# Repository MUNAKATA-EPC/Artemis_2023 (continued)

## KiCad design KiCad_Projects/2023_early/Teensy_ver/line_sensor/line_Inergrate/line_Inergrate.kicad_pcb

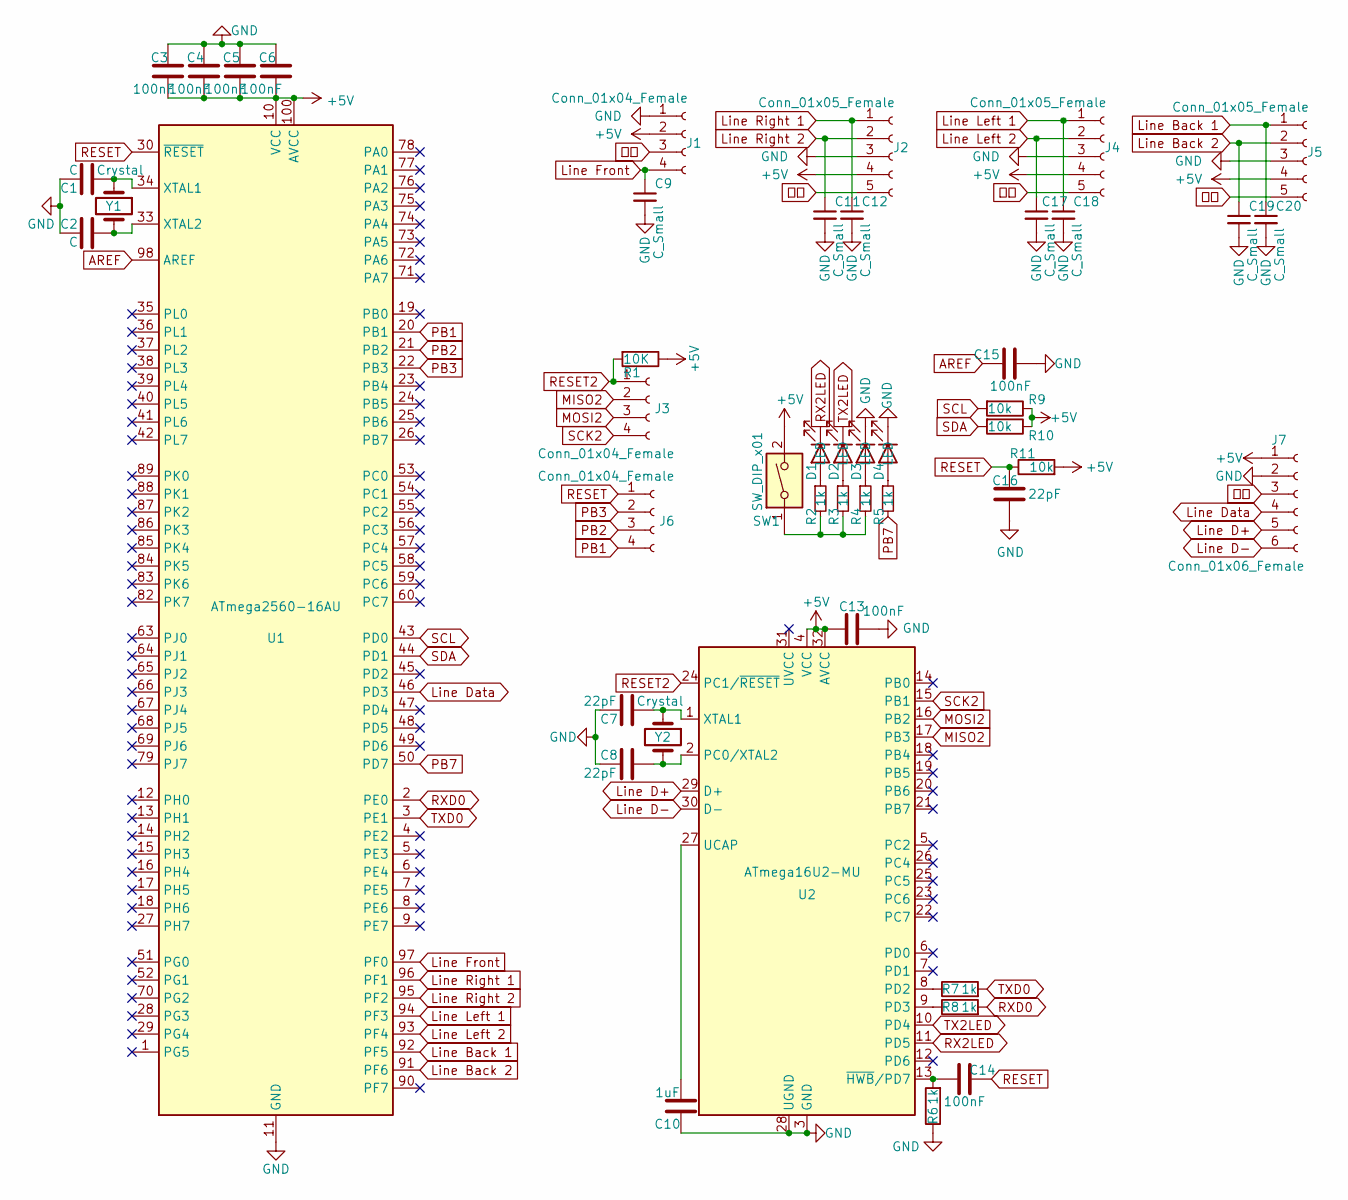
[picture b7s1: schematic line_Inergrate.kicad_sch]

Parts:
C1, C2: C; C_0402_1005Metric; LCSC C1555
C3, C4, C5, C6, C13, C14, C15: 100nF; C_0402_1005Metric; LCSC C41851
C7, C8, C16: 22pF; C_0402_1005Metric; LCSC C1555
C9, C11, C12, C17, C18, C19, C20: C_Small; C_Disc_D3.0mm_W1.6mm_P2.50mm
C10: 1uF; C_0402_1005Metric; LCSC C167339
D1, D2, D3, D4: LED; LED_0402_1005Metric; LCSC C130725
J1: Conn_01x04_Female; PinSocket_1x04_P2.54mm_Horizontal
J2, J4, J5: Conn_01x05_Female; PinSocket_1x05_P2.54mm_Horizontal
J3, J6: Conn_01x04_Female; PinSocket_1x04_P2.54mm_Vertical
J7: Conn_01x06_Female; JST_XH_B6B-XH-A_1x06_P2.50mm_Vertical
R1: 10K; R_0402_1005Metric; LCSC C25744
R2, R3, R4, R5: 1k; R_0402_1005Metric; LCSC C11702
R6, R7, R8: 1k; R_0402_1005Metric; LCSC C105637
R9, R10, R11: 10k; R_0402_1005Metric; LCSC C25744
SW1: SW_DIP_x01; 2MS1T2B4M2QES
U1: ATmega2560-16AU; TQFP-100_14x14mm_P0.5mm
U2: ATmega16U2-MU; QFN-32-1EP_5x5mm_P0.5mm_EP3.1x3.1mm
Y1, Y2: Crystal; Crystal_SMD_3225-4Pin_3.2x2.5mm; LCSC C164049

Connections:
Line Left 1: C18.1, J4.1, U1.94 (PF3)
+5V: C3.2, C4.2, C5.2, C6.2, C13.2, J1.2, J2.4, J4.4, J5.4, J7.1, R1.1, R9.1, R10.1, R11.2, SW1.2, U1.10 (VCC), U1.31 (VCC), U1.61 (VCC), U1.80 (VCC), U1.100 (AVCC), U2.4 (VCC), U2.32 (AVCC)
AREF: C15.1, U1.98 (AREF)
GND: C1.2, C2.2, C3.1, C4.1, C5.1, C6.1, C7.2, C8.2, C9.2, C10.2, C11.2, C12.2, C13.1, C15.2, C16.2, C17.2, C18.2, C19.2, C20.2, D3.1 (K), D4.1 (K), J1.1, J2.3, J4.3, J5.3, J7.2, R6.1, U1.11 (GND), U1.32 (GND), U1.62 (GND), U1.81 (GND), U1.99 (GND), U2.3 (GND), U2.28 (UGND), U2.33 (GND)
Line Back 1: C20.1, J5.1, U1.92 (PF5)
Line Back 2: C19.1, J5.2, U1.91 (PF6)
Line D+: J7.5, U2.29 (D+)
Line D-: J7.6, U2.30 (D-)
Line Data: J7.4, U1.46 (PD3)
Line Front: C9.1, J1.4, U1.97 (PF0)
Line Left 2: C17.1, J4.2, U1.93 (PF4)
Line Right 1: C12.1, J2.1, U1.96 (PF1)
Line Right 2: C11.1, J2.2, U1.95 (PF2)
MISO2: J3.2, U2.17 (PB3)
MOSI2: J3.3, U2.16 (PB2)
unnamed: C1.1, U1.34 (XTAL1), Y1.1
unnamed: C2.1, U1.33 (XTAL2), Y1.2
unnamed: C7.1, U2.1 (XTAL1), Y2.1
unnamed: C8.1, U2.2 (PC0/XTAL2), Y2.2
unnamed: C10.1, U2.27 (UCAP)
unnamed: C14.1, R6.2, U2.13 (~HWB/PD7)
unnamed: D1.2 (A), R2.1
unnamed: D2.2 (A), R3.1
unnamed: D3.2 (A), R4.1
unnamed: D4.2 (A), R5.1
unnamed: R2.2, R3.2, R4.2, SW1.1
unnamed: R7.1, U2.8 (PD2)
unnamed: R8.1, U2.9 (PD3)
PB1: J6.4, U1.20 (PB1)
PB2: J6.3, U1.21 (PB2)
PB3: J6.2, U1.22 (PB3)
PB7: R5.2, U1.50 (PD7)
RESET: C14.2, C16.1, J6.1, R11.1, U1.30 (~RESET)
RESET2: J3.1, R1.2, U2.24 (PC1/~RESET)
RX2LED: D1.1 (K), U2.11 (PD5)
RXD0: R8.2, U1.2 (PE0)
SCK2: J3.4, U2.15 (PB1)
SCL: R9.2, U1.43 (PD0)
SDA: R10.2, U1.44 (PD1)
TX2LED: D2.1 (K), U2.10 (PD4)
TXD0: R7.2, U1.3 (PE1)
可変: J1.3, J2.5, J4.5, J5.5, J7.3

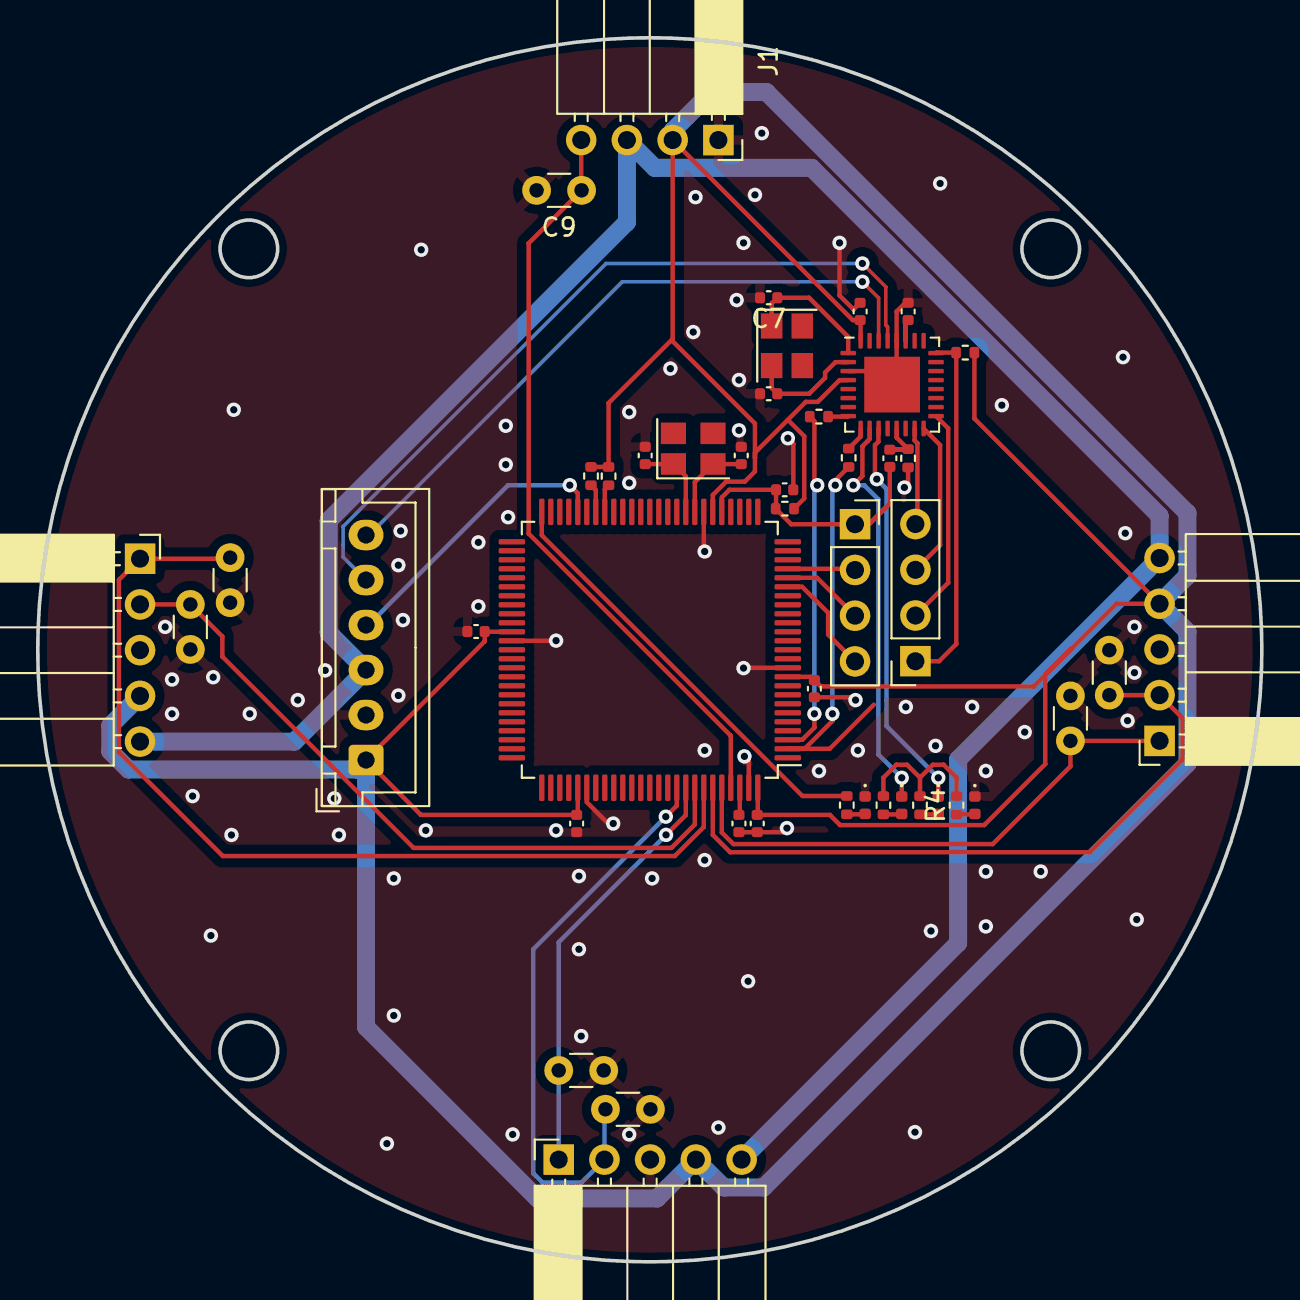
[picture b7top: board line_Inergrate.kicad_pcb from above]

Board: 2 copper layers, 68.0 x 68.0 mm, 46 parts (0 on the bottom side), 42 nets.

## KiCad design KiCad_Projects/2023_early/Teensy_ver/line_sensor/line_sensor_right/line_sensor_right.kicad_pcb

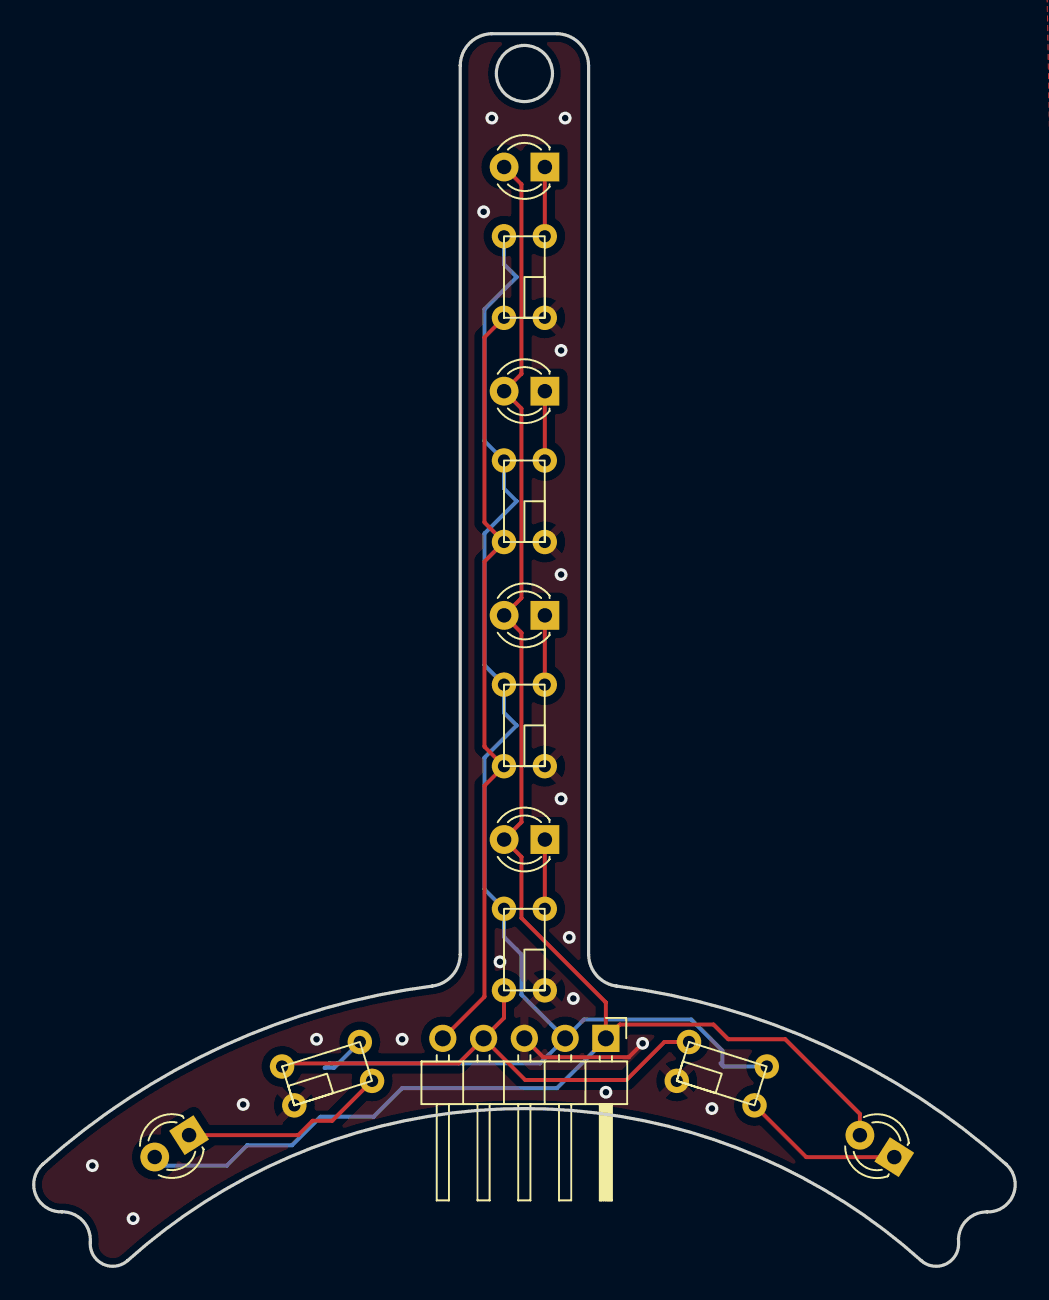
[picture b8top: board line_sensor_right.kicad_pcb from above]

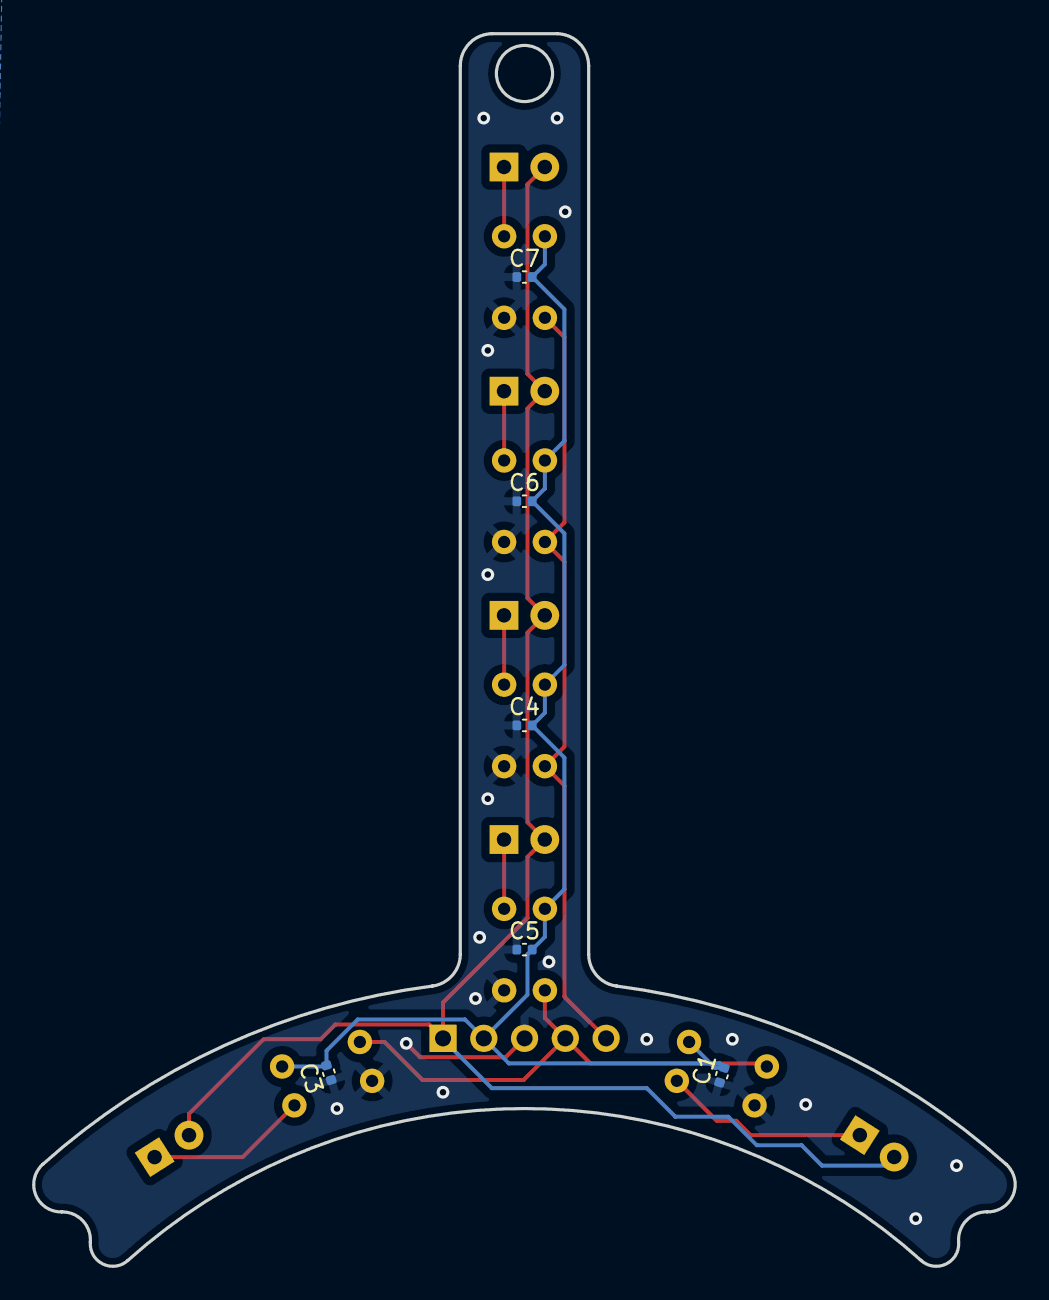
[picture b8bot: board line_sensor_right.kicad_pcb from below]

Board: 2 copper layers, 61.2 x 76.8 mm, 19 parts (6 on the bottom side), 11 nets.

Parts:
C1, C3, C4, C5, C6, C7: C_Small; C_0402_1005Metric
D1, D3, D4, D5, D6, D7: LED; LED_D3.0mm_Clear
J1: Conn_01x05_Female; PinHeader_1x05_P2.54mm_Horizontal
U1, U3, U4, U5, U6, U7: Line_sennsor

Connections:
+5V: C1.2, C3.2, C4.2, C5.2, C6.2, C7.2, J1.2, U1.2 (VCC), U3.2 (VCC), U4.2 (VCC), U5.2 (VCC), U6.2 (VCC), U7.2 (VCC)
GND: C1.1, C3.1, C4.1, C5.1, C6.1, C7.1, J1.3, U1.4 (GND), U3.4 (GND), U4.4 (GND), U5.4 (GND), U6.4 (GND), U7.4 (GND)
Line Data 1: J1.4, U1.3 (VOUT), U3.3 (VOUT), U5.3 (VOUT)
Line Data 2: J1.5, U4.3 (VOUT), U6.3 (VOUT), U7.3 (VOUT)
unnamed: D1.1 (K), U1.1 (K(-))
unnamed: D3.1 (K), U3.1 (K(-))
unnamed: D4.1 (K), U4.1 (K(-))
unnamed: D5.1 (K), U5.1 (K(-))
unnamed: D6.1 (K), U6.1 (K(-))
unnamed: D7.1 (K), U7.1 (K(-))
R Trim: D1.2 (A), D3.2 (A), D4.2 (A), D5.2 (A), D6.2 (A), D7.2 (A), J1.1

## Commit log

2022-04-20 Initial Commit
    最初のコミットです。
    各ファイルを追加。
2022-04-20 進捗追加
    githubリポジトリを作成
2022-04-21 Revert "Update New-Robo-DesignMemo.txt"
    This reverts commit f9405847499580822d066fcdcb91f958b3cb44ed.
2022-04-21 ジャイロセンサ用ファイルの生成
    VSCode(PlatformIO)の自動生成ファイル
2022-04-21 CADデータ用ファイル追加
2022-04-21 .gitkeepファイルの追加
    このファイルは空フォルダがコミット内容として反映されるために追加する空ファイルです。
    ディレクトリを作成した際に中身が空だった場合は.gitkeepファイルを生成してコミット内容に反映してください。
2022-04-21 空フォルダの反映
    .gitkeepファイルの追加
2022-04-21 README.MD の追加によるファイル削除
    ロボットの情報をREADME.MDに追加したことによるファイルの削除。
    要望があったらまた追加します。
2022-04-21 Revert "フレーム 現状 Artemis機"
    This reverts commit 175b8af8b3617812aba4bc7054874700fb0bbe0f.
2022-04-27 DSR1202用のライブラリ追加
    https://github.com/anbara/DSR-1202 より引用
2022-04-29 過去ファイル追加&ジャイロプロジェクト名変更
    福岡ノード2021用のフォルダ作成。
    過去のプログラム置き場作成。
    ジャイロをMPU6050からL3GD20に変更。
2022-05-03 MPU6050用のジャイロファイルをリターン・ファイル整理
    MPU6050用のプログラムを保存しておきます
    あとファイルをまとめておきました。
2022-05-03 セカンドロボットの文化祭用プログラム追加
    ジャイロと電源の部分一緒に作ってるから
    pid動かないと思うの！！！！(正解)
2022-05-03 readme.mdにライセンス追加
2022-06-01 KiCadプロジェクト保存用フォルダの作成
    バックアップはちゃんと取りましょう。
2022-06-01 部品ごとのデータファイルの追加
    マイコンのシンボル、基板のデータ保存用のファイル等の追加
2022-06-01 omuniのCADデータの追加
    各部品のデータの追加
    ３Dプリンター用のデータにも変換済み
2022-06-07 KiCadの各プロジェクトの追加
    各シンボルのライブラリ・プロジェクトの追加
2022-06-07 シンボルライブラリのパス指定を絶対パスから相対パスへ変更。
    環境によってプロジェクトの配置階層が変わるのでプロジェクトから見た相対パスへ変更。
    ${KIPRJMOD}/../Lib/(project_name)
    で指定可能なのでこれからはそうすること。
2022-06-07 メイン基板の更新
    IRセンサー等のセンサー追加、配線追加。
2022-06-08 メイン基板の更新
    IRセンサの配線変更等
2022-06-09 メイン基板の更新
    内容は知らないです
2022-06-09 基板の更新
    メイン基板の更新、ライブラリの追加
    ※電源基盤はいまだ理解できずに手が付けられてない。
2022-06-12 基板データの更新
    メイン基板、電源基盤のデータ更新
    回路が正しいか答え合わせするもんなくで困ってる。ダレカタスケテ
2022-06-13 基板データの更新
    電源回路の更新、ライブラリの追加
    やっと回路理解してきた！
2022-06-14 基板データの更新
    電源基盤の更新、フットプリントの割り当て中
2022-06-17 基盤データの更新
    電源基盤のフットプリントの割り当て完了
    配線開始。
2022-06-20 基盤データの更新
    フットプリントの更新、電源基盤の部品の配置
2022-06-22 電源基盤の更新
    基盤の外形のインポート、部品の配置。
2022-06-24 基盤データの更新
    電源基盤、IOボードの配線更新。
2022-06-24 基盤データの更新
    メイン基板の回路図の更新
2022-06-29 基盤データのアップデート
    ローカルコミットはちゃんと作ってください
2022-06-29 基板データの更新
    ラインセンサーの完成
    Arduino メイン基板の作成、製作開始。
2022-06-30 基板データの更新
    IO基板、ライン基板、電源基盤のコネクタ変更、最終確認
    メイン基板制作中。
2022-07-01 基板データの更新
    メイン基板の製作
2022-07-02 基板データの更新
    メイン基板の部品配置まででけた
2022-07-03 AE-BNO055-BO専用のプロジェクト追加
2022-07-10 基板データの更新
    最後に更新してからのデータ全てです。
2022-07-10 基板データの更新
    今日変更した分
    メイン基板
2022-07-11 基板データの更新
    最新バージョンの発注データの作成
    最新バージョンの発注。
2022-07-13 基板データの更新
    メイン基板データの更新
2022-07-18 基板データの更新
    IO基板のCNCバージョン作成
2022-07-18 基板データの更新
    IO基板
2022-07-18 部内大会用のプログラムファイル追加
    タイトル通り。
    松田の前代ロボに関してはプログラムはほぼ完ぺき。
2022-07-18 基板データの更新
    新メイン基板の回路図の作成。
2022-07-18 Revert "Merge branch 'main' of https://github.com/MUNAKATA-EPC/Munachu_Artemis"
    This reverts commit 2d62b7fa3f437b1c22d560bdfdc29bbce9a662c6, reversing
    changes made to e44e47092be221c5dedf368005a17df58de841e6.
2022-07-24 基板データの更新
2022-07-24 Dual core TJ3B ファイルの作成
    ただいまスレーブを用いた20ポートTJ3Bの製作中です。
    今、回路設計中。
2022-07-27 基板データの更新
    新メイン基板あたりをいじった
2022-07-28 部内大会用プログラムの作成
    部内大会というか、北九州オープンくらいまでのプログラムが入ってます。
    カメラ・IR_ring・Line_ringの制御。
2022-07-28 基板データの更新
    いろいろいじったものの更新です。
    MD用のファイルの追加もしました。
2022-07-31 Gitの変更多すぎだろ！
    ここに覚えてる限りの変更点をまとめます
    ・カメラのプログラム
    ・IR_ringプログラム
    ・メインプログラム(Artemis機)
    ・ジャイロプログラム
    ・基盤データ
2022-07-31 プレゼンシート用ファイルの追加・不要ファイルの削除
    テストプログラムの削除。
    プレゼンテーションシート用画像・フォルダの追加。
2022-07-31 部品の３Dデータのアップロード
    Designファイルの追加
    各部品用のファイル・データの追加
2022-07-31 ロボット全体像の３Dデータの追加
2022-08-02 プレゼンシート更新
2022-08-02 プレゼンシートあらかた完成
2022-08-03 プレゼンシートの更新
    あんましいじってないですが、
2022-08-04 謎ファイル削除
2022-08-05 プレゼンシートの更新
2022-08-07 北九州オープンプログラム最新版
    最新です
2022-08-08 ジャイロセンサのプログラム修正
    kitakore
2022-08-09 GoalPID仮実装
    動くかしらん
2022-08-10 参考資料用ファイル追加
    ロボット、CAD、プログラムについてなどのPDFなどの参考資料を保存するファイルの追加。
    自由にファイルを作って追加してください。
    写真なども可
2022-08-12 基板データの更新
    新メイン基板のデータの更新
2022-08-12 基板データの更新
    新メイン基板の更新
2022-08-23 ファイル構成変更
2022-08-23 ファイル構成変更
    megaに移行するため
2022-08-28 CADデータの追加、更新
    各基盤のファイル、データの追加
    Fusion360の新ロボの設計のデータ追加
2022-10-13 ロボットのハード関係のデータ更新
    今までため込んでた３Dデータ、基板データの更新です。
    Teensy機の基板があと少しですべて終わる
2022-11-23 プログラム変更
    変更多すぎて草
2022-11-26 ロボチャレようのプレゼンシート、現在のプログラムを更新
    がんばるぞー！！
2022-11-26 OpenMVのプログラム追加
2022-11-27 ロボチャレ用プログラム！
    お疲れ
2022-12-06 ハードのデータ更新
    いろいろたまって申し訳ない
    ハード全般のデータ更新です。
    ついでに、2023シーズン用のプレゼンシートも上げときます。（未完成）
2022-12-09 プログラム更新
    C-Code勢 に 進化した！
2022-12-09 いろいろ調整
2022-12-09 プログラム調整
2022-12-10 フォルダ名変更
    これでわかりやすいはず！
2022-12-14 Update main program of the first robo
    also update ir program(using vector)
2022-12-24 プログラム更新！！！！
    チームの画像も追加してます
    カメラは自動的に色鳥するように
2022-12-24 ごみPC
2023-01-06 九州ブロック用二機プログラム完成！！
    ぼくがかんがえたさいきょうのぷろぐらむ
2023-02-27 基板データの更新
    1318のファイルがたまってました
    多くなって申し訳ない
2023-02-27 プレゼンシートの更新
    内容が古かったので最新に置き換えた
2023-03-06 頑張った
2023-03-13 For JapanOpen
2023-03-13 プログラム・プレゼンシートの更新
2023-03-14 プログラム追加
2023-03-14 大会用ファイルの追加
2023-03-15 Update Program and PresentationSheet
2023-03-15 completed presentation task
2023-03-18 基板データの更新
    あうあうあー
2023-03-20 全国まであと一日ってマ？
2023-03-20 動くかわからん系プログラムLetsGOOOOOOO
2023-03-22 update programs
2023-03-22 なんかの更新
2023-03-23 Program Update
2023-03-23 unko6ggr
    hyh
2023-03-23 prog
2023-03-24 unkoo
2023-04-12 update files
2023-04-12 公開用にデータを変更
2023-05-24 Untitled-2023-05-24_220913
    ライン統合基板
2023-05-24 目野のデータ開いたことによる変更？
    開いたら変更扱いされたから上げとく
2023-05-24 Untitled-2023-05-24_220913.zip
    ライン統合基板
2023-05-24 開いたことによる更新
2023-05-26 文化祭用プリンデータの追加
2023-06-04 KiCAD ジャイロ基板の更新
2023-07-15 なんかたまってたので上げます。
    知らんうちに変更がたまってたので上げます。
2023-07-18 東郷コミセン用
2023-07-31 bunaitaikai
2023-08-03 anyaanya
    aaaaaaa
2024-03-28 なんか残ってた
